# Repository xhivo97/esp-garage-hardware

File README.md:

**NOTE:** The hardware is in its early development. This is meant to replace your garage opener, if you'd like to use this with your existing garage door opener only slight modifications are needed. As of now relays control the motor, in the future there will be a motor driver circuit integrated on the PCB.

# Hardware for esp-garage

ESP32-C3 based garage opener PCB.

You can find the firmware [here](https://github.com/xhivo97/esp-garage-firmware)

## Possible issues

If you build this and the board resets when pulling high currents you may need to add a capacitor between `IN+` and `IN-`.

## TO-DO List

- [ ] Hardware modifications.
    > Add input protection.

    > Add USB polyfuse and ESD protection.

    > Add on-board LEDs and remove the light relay.

    > Add motor controller circuit and remove relays A and B.

    > Add light sensor GPIO connector.

    > Integrate batteries on the PCB, if 4 cells are not enough consider external battery packs instead.

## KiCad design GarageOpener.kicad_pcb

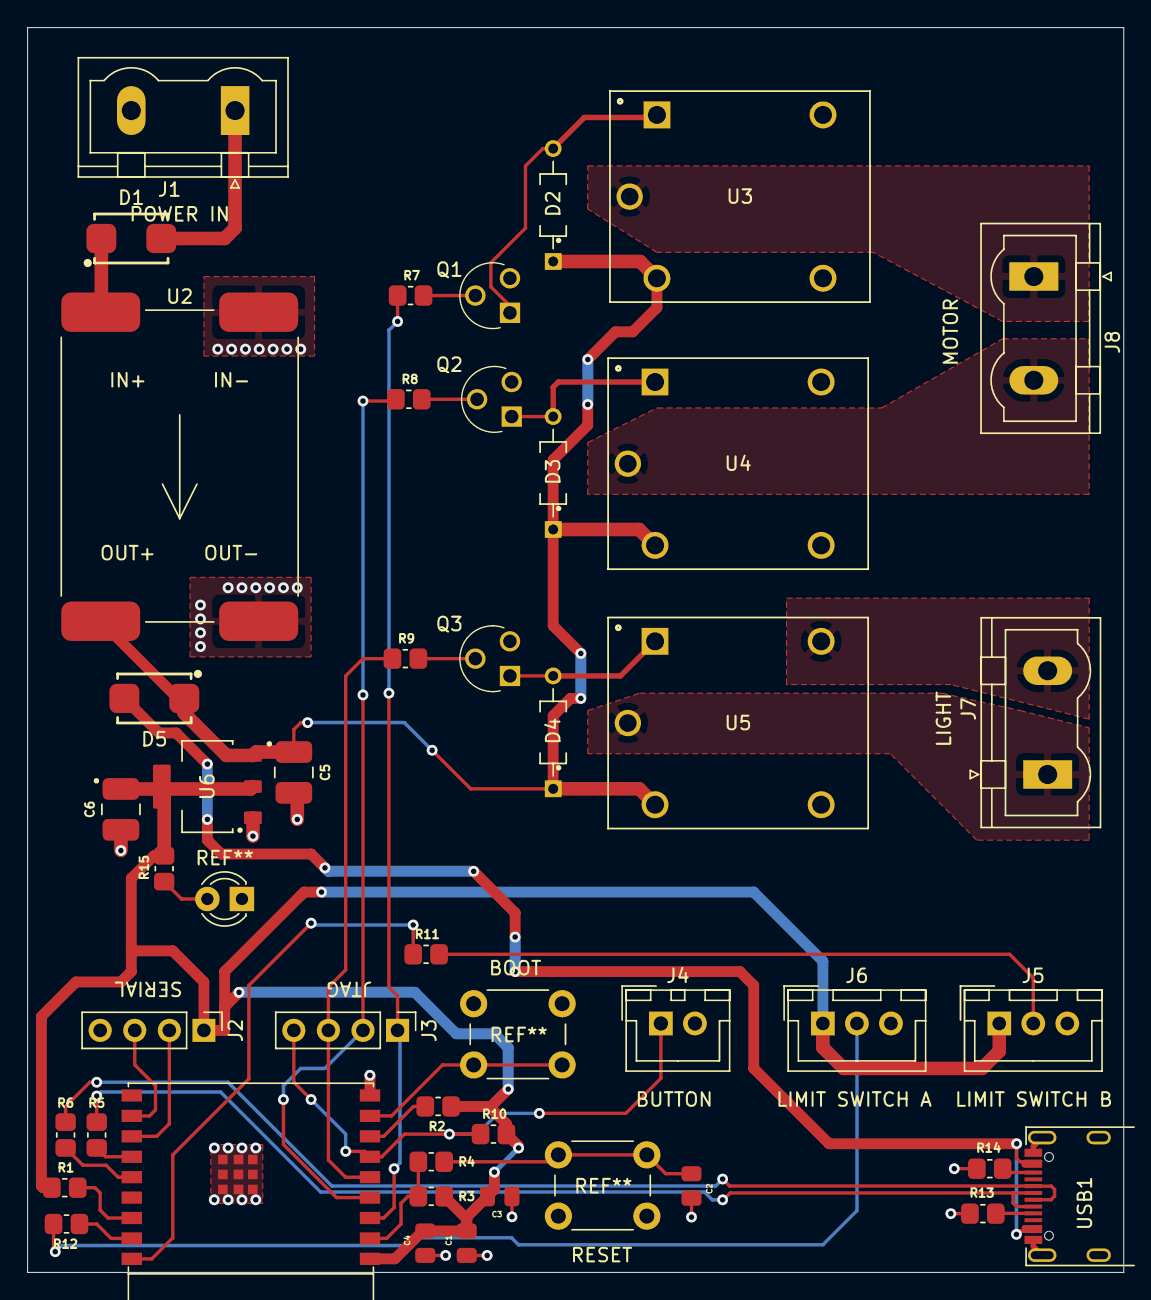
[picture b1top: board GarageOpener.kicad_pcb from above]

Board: 2 copper layers, 80.5 x 91.4 mm, 47 parts (0 on the bottom side), 37 nets.

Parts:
C1: 10uF; CAPC2012X145N
C2, C4: 100nF; CAPC2012X145N
C3: 1uF; CAPC2012X145N
C5, C6: 10uF_tantalum; CAP_16TQC10M
D1, D5: STPS1H100U; DIOM5436X245N
D2, D3, D4: 1N4148; DIOAD829W49L456D191
D6: LED; LED_D3.0mm
J1, J7, J8: 7.62mm-2pin; PhoenixContact_GMSTBVA-G_02x7.62mm_Vertical
J2, J3: 1x4pin; PinHeader_1x04_P2.54mm_Vertical
J4: JST-XH-2; JST_XH_B02B-XH-A_02x2.50mm_Straight
J5, J6: JST-XH-3; JST_XH_B03B-XH-A_03x2.50mm_Straight
Q1, Q2, Q3: BC547B; TO127P254X732-3
R1, R2, R3, R10: 10k; RESC2012X60
R4, R5, R6: 0R; RESC2012X60
R7, R8, R9, R11, R12, R13, R14, R15: 5k1; RESC2012X60
SW1, SW2: Switch; SW_PUSH_6mm
U1: ESP32-C3-WROOM-02
U2: dc-dc_3A5V; dc-dc_converter_module
U3, U4, U5: G5LA-14-DC5; RELAY_SRD-05VDC-SL-C
U6: AMS1117-3.3; SOT229P700X180-4N
USB1: U262-161N-4BVC11; XKB-USB-C-16P

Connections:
5V_IN: C5.1, D2.C, D3.C, D4.C, D5.C, U2.O+, U3.A2, U4.A2, U5.A2, U6.3
5V_USB: D5.A, USB1.A4, USB1.A9, USB1.B4, USB1.B9
24V_IN: D1.A, J1.1, U3.NO, U4.NO, U5.NO
BOOT: SW2.1, U1.8
EN: R3.1, R4.2, U1.2
GND: C1.1, C2.2, C3.1, C4.1, C5.2, C6.2, D6.C, J1.2, J2.4, J4.2, J5.3, J6.3, J7.2, Q1.3, Q2.3, Q3.3, R13.2, R14.2, SW1.1, SW2.2, U1.9, U1.19, U2.I-, U2.O-, U3.NC, U4.NC, U5.NC, U6.1, USB1.A1, USB1.A12, USB1.B1, USB1.B12, USB1.S1
IO0: R11.1, U1.18
IO1: R12.1, U1.17
IO4: J3.1, R7.1, U1.3
IO5: J3.2, R8.1, U1.4
IO6: J3.3, R9.1, U1.5
IO7: J3.4, J4.1, R10.1, U1.6
MOTOR_A: J8.1, U3.COM
MOTOR_B: J8.2, U4.COM
unnamed: C2.1, R4.1, SW1.2
unnamed: D1.C, U2.I+
unnamed: D2.A, Q1.1, U3.A1
unnamed: D3.A, Q2.1, U4.A1
unnamed: D4.A, Q3.1, U5.A1
unnamed: D6.A, R15.1
unnamed: J5.2, R11.2
unnamed: J6.2, R12.2
unnamed: J7.1, U5.COM
unnamed: R1.2, U1.16
unnamed: R2.2, U1.7
unnamed: R5.1, U1.13
unnamed: R6.1, U1.14
unnamed: R13.1, USB1.A5
unnamed: R14.1, USB1.B5
RELAY_A: Q1.2, R7.2
RELAY_B: Q2.2, R8.2
RELAY_LIGHT: Q3.2, R9.2
RXD: J2.3, U1.11
TXD: J2.2, U1.12
USBD+: R6.2, USB1.A6, USB1.B6
USBD-: R5.2, USB1.A7, USB1.B7
VDD33: C1.2, C3.2, C4.2, C6.1, J2.1, J5.1, J6.1, R1.1, R2.1, R3.2, R10.2, R15.2, U1.1, U6.2, U6.TAB

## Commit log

2021-11-20 Added missing zones
